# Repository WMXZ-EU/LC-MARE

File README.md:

# LC-MARE
Low-Cost Marine Acoustic REcorder. See detailed info in different folders
 
Actual preferred firmware verson is adalogger_V3

## Content
### 3D-models
contains some stl files for 3D printing
### adalogger_V2
first LC-Mare firmware uses only adalogger RP2040. Suitable for single hydrophone and sampling frequency up to 96 kHz
### adalogger_V3
improved LC-Mare firmware 
- for adalogger RP2040 (single hydrophone up to 96 kHz sampling frequency)
- for rp2350 based adafruit feather (stereo and up to 384 kHz sampling frequency)
### microPAM_V3
improved version of adalogger_V3 for three MCU types (RP2040, RP2350, Teensy4.1)
all for sampling frequency up to 384 kHz

As of Nov-2026, this is the suggested firmware.

Read the README.pdf and setup.pdf for general description and setup instructions

the latest release may be found in

https://github.com/WMXZ-EU/LC-MARE/releases/latest/download/microPAM_V3.zip

### Documents
different files describing project and hardware construction
### KICAD
hardware desigh files for
- ADC (ADC_V2)
- preamp (PreampV5-mare)
- Base board (LC_PAMV4b)
- Libraries (for KICAD)
### Python
contains python based setup and analysis scripts for adalogger software

Of importance is a GUI (LC_Mare.py) that provides access to basic operations, like inspecting LC_mare file parameters, visualizing time series and spectra, to configure the firmware, to convert compressed to wav files, and to upload latest firmware

An compiled version for adalogger software (.exe) with supporting libraries may be found in

https://github.com/WMXZ-EU/LC-MARE/releases/download/LC_Mare_v1.0.0/LC_Mare.zip

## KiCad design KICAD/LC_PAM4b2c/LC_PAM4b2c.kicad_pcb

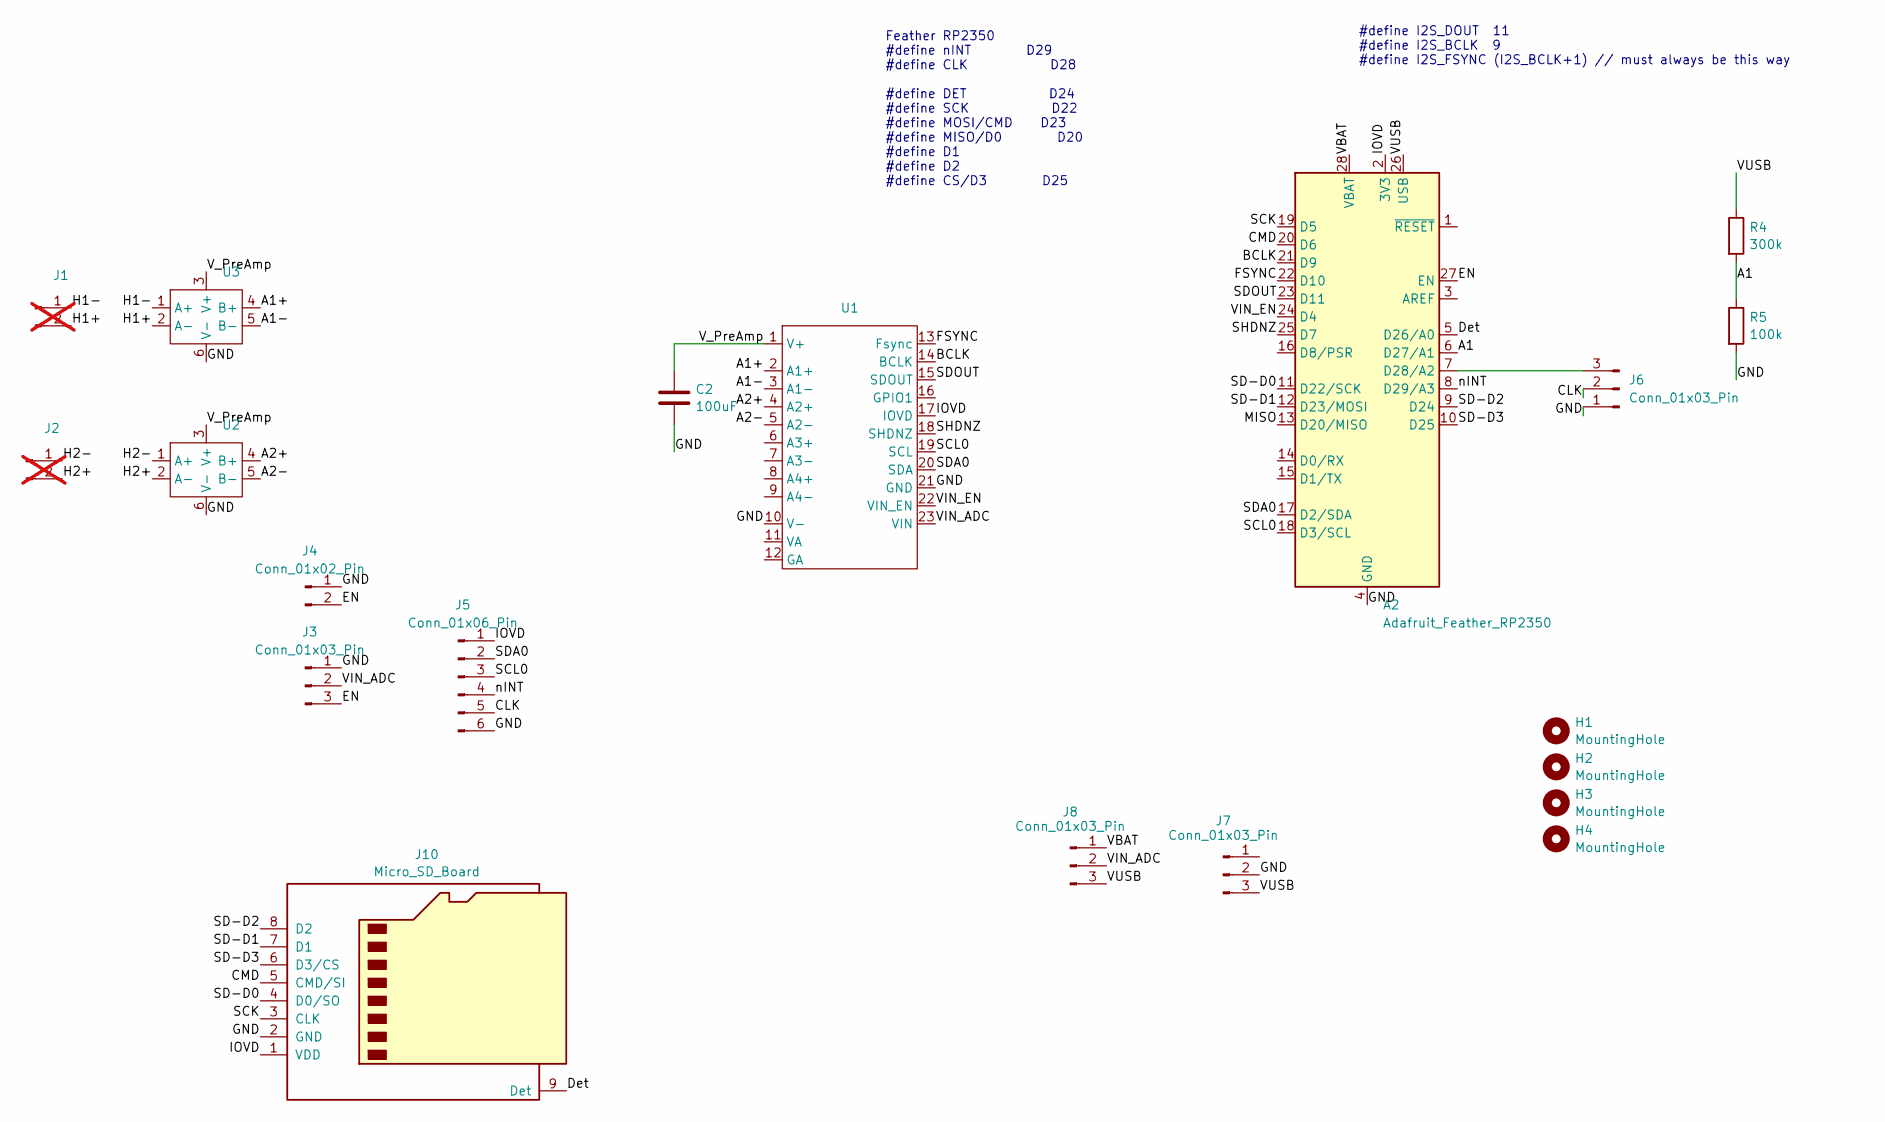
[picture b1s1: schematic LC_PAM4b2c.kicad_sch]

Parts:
A2: Adafruit_Feather_RP2350; Adafruit_Feather
C2: 100uF; CP_Radial_D4.0mm_P2.00mm
H1, H2, H3, H4: MountingHole; MountingHole_3.2mm_M3_DIN965
J1, J2: Conn_01x02_Male; Molex_PicoBlade_53048-0210_1x02_P1.25mm_Horizontal; not fitted
J3, J7, J8: Conn_01x03_Pin; PinHeader_1x03_P2.54mm_Vertical
J4: Conn_01x02_Pin; PinHeader_1x02_P2.54mm_Vertical
J5: Conn_01x06_Pin; PinHeader_1x06_P2.54mm_Vertical
J6: Conn_01x03_Pin; PinHeader_1x03_P1.27mm_Vertical
J10: Micro_SD_Board; uSD
R4: 300k; R_Axial_DIN0204_L3.6mm_D1.6mm_P1.90mm_Vertical
R5: 100k; R_Axial_DIN0204_L3.6mm_D1.6mm_P1.90mm_Vertical
U1: ADC_V2
U2, U3: preAmp2

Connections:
/A1: A2.6 (D27/A1), R4.2, R5.1
/A1+: U1.2 (A1+), U3.4 (B+)
/A1-: U1.3 (A1-), U3.5 (B-)
/A2+: U1.4 (A2+), U2.4 (B+)
/A2-: U1.5 (A2-), U2.5 (B-)
/BCLK: A2.21 (D9), U1.14 (BCLK)
/CLK: J5.5, J6.2
/CMD: A2.20 (D6), J10.5 (CMD/SI)
/Det: A2.5 (D26/A0), J10.9 (Det)
/EN: A2.27 (EN), J3.3, J4.2
/FSYNC: A2.22 (D10), U1.13 (Fsync)
/GND: A2.4 (GND), C2.2, J3.1, J4.1, J5.6, J6.1, J7.2, J10.2 (GND), R5.2, U1.10 (V-), U1.21 (GND), U2.6 (V-), U3.6 (V-)
/H1+: J1.2, U3.2 (A-)
/H1-: J1.1, U3.1 (A+)
/H2+: J2.2, U2.2 (A-)
/H2-: J2.1, U2.1 (A+)
/IOVD: A2.2 (3V3), J5.1, J10.1 (VDD), U1.17 (IOVD)
/MISO: A2.13 (D20/MISO)
/SCK: A2.19 (D5), J10.3 (CLK)
/SCL0: A2.18 (D3/SCL), J5.3, U1.19 (SCL)
/SD-D0: A2.11 (D22/SCK), J10.4 (D0/SO)
/SD-D1: A2.12 (D23/MOSI), J10.7 (D1)
/SD-D2: A2.9 (D24), J10.8 (D2)
/SD-D3: A2.10 (D25), J10.6 (D3/CS)
/SDA0: A2.17 (D2/SDA), J5.2, U1.20 (SDA)
/SDOUT: A2.23 (D11), U1.15 (SDOUT)
/SHDNZ: A2.25 (D7), U1.18 (SHDNZ)
/VBAT: A2.28 (VBAT), J8.1
/VIN_ADC: J3.2, J8.2, U1.23 (VIN)
/VIN_EN: A2.24 (D4), U1.22 (VIN_EN)
/VUSB: A2.26 (USB), J7.3, J8.3, R4.1
/V_PreAmp: C2.1, U1.1 (V+), U2.3 (V+), U3.3 (V+)
/nINT: A2.8 (D29/A3), J5.4
unnamed: A2.7 (D28/A2), J6.3

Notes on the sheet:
Feather RP2350 #define nINT D29 #define CLK D28 #define DET D24 #define SCK D22 #define MOSI/CMD D23 #define MISO/D0 D20 #define D1 #define D2 #define CS/D3 D25
#define I2S_DOUT 11 #define I2S_BCLK 9 #define I2S_FSYNC (I2S_BCLK+1) // must always be this way

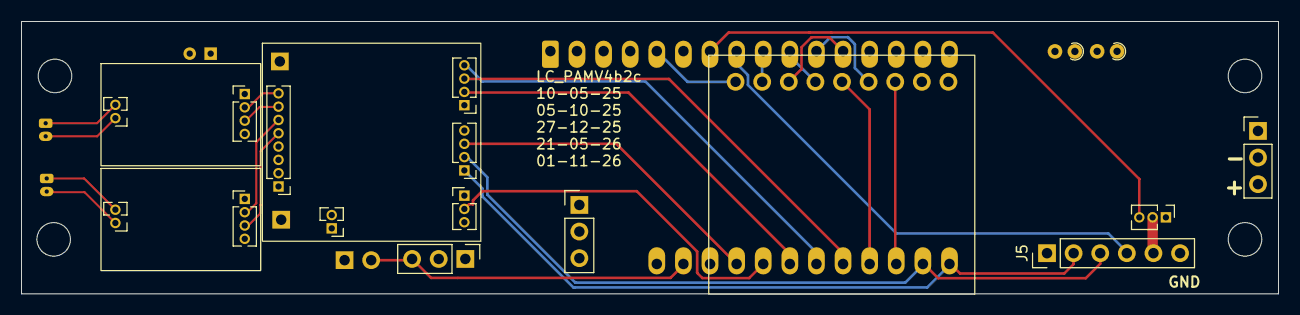
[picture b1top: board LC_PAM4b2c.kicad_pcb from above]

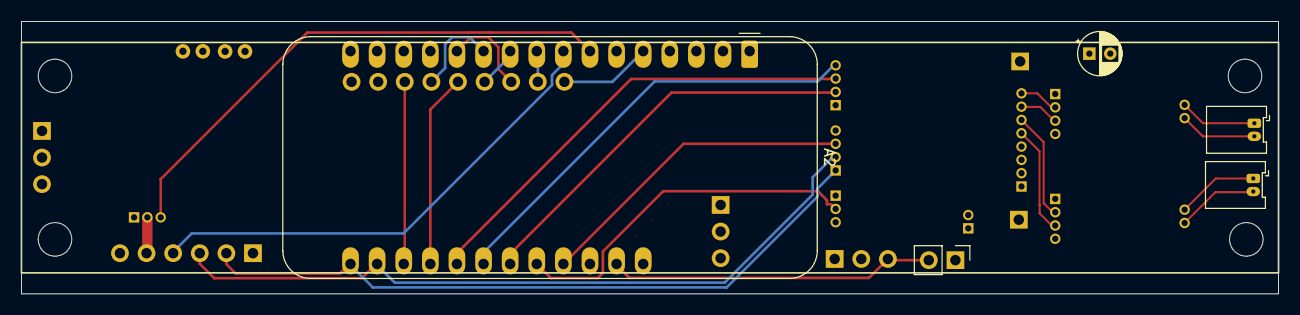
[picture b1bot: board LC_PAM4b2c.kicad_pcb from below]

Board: 4 copper layers, 120.0 x 26.0 mm, 20 parts (5 on the bottom side), 33 nets.

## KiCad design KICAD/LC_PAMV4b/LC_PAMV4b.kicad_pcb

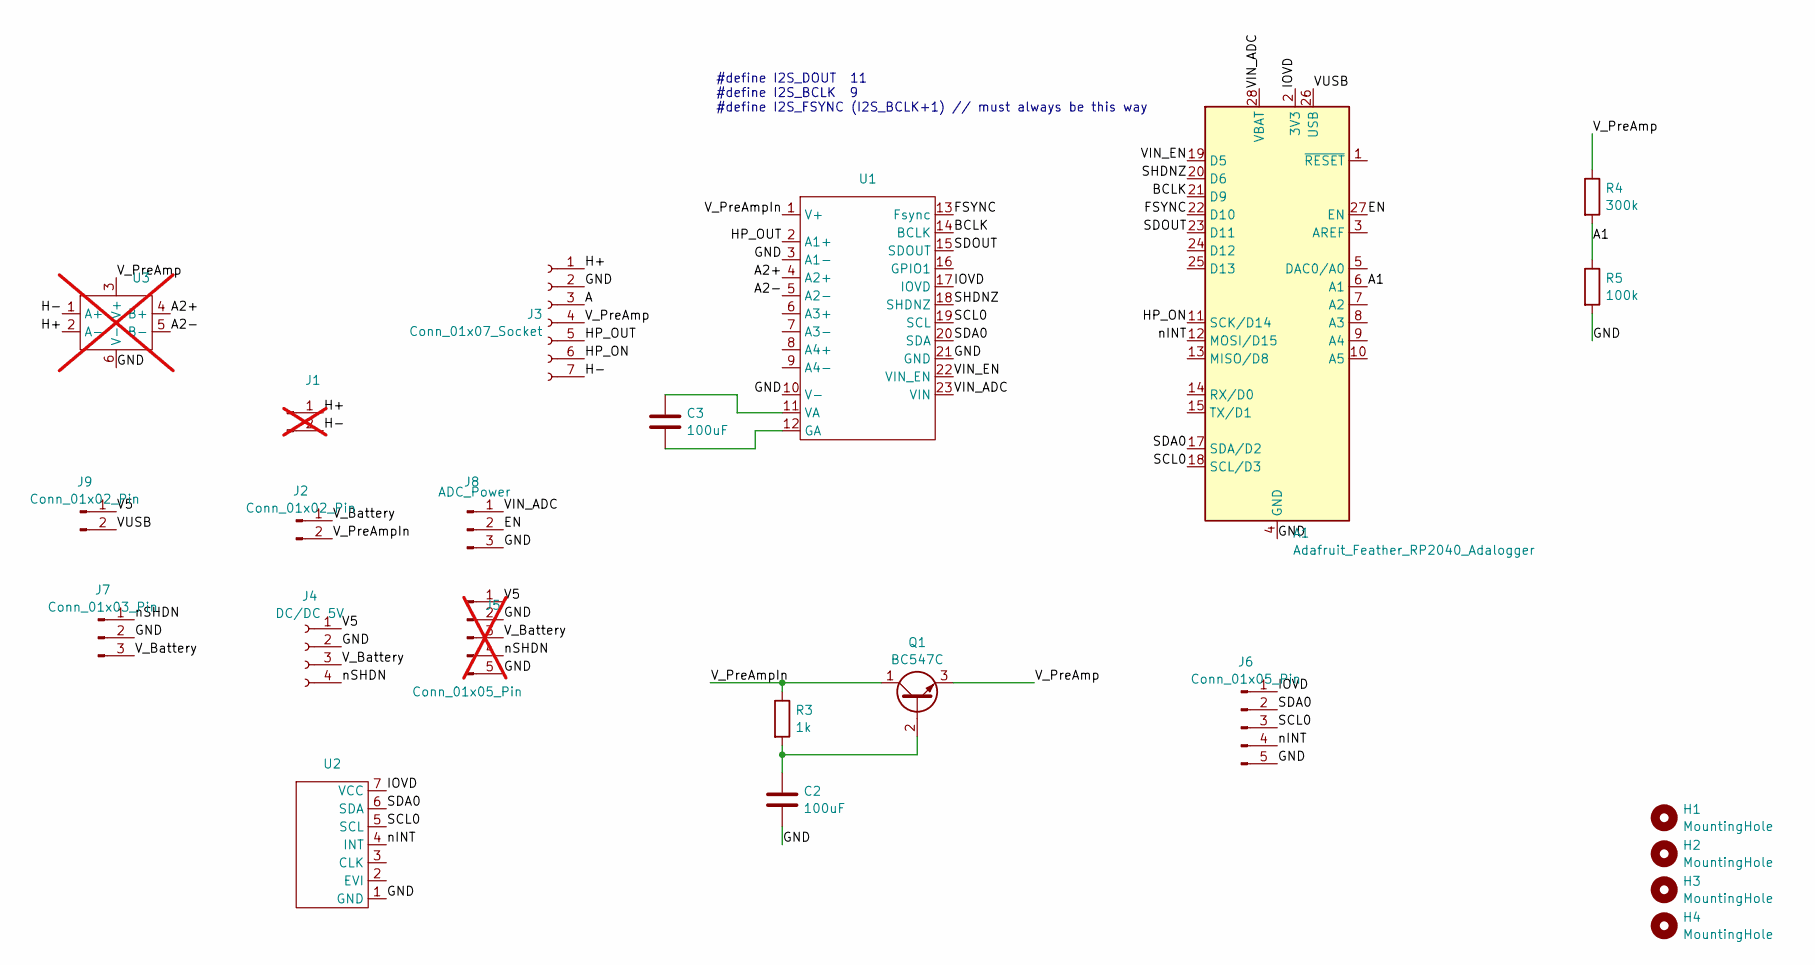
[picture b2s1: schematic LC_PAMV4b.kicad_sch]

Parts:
A1: Adafruit_Feather_RP2040_Adalogger; Adafruit_Feather_WithMountingHoles
C2, C3: 100uF; CP_Radial_D4.0mm_P2.00mm
H1, H2, H3, H4: MountingHole; MountingHole_3.2mm_M3_DIN965
J1: Conn_01x02_Male; Molex_PicoBlade_53048-0210_1x02_P1.25mm_Horizontal; not fitted
J2, J9: Conn_01x02_Pin; PinHeader_1x02_P2.00mm_Vertical
J3: Conn_01x07_Socket; HPAB
J4: DC/DC 5V; PinHeader_1x04_P2.54mm_Vertical
J5: Conn_01x05_Pin; PinHeader_1x05_P2.54mm_Vertical; not fitted
J6: Conn_01x05_Pin; PinHeader_1x05_P2.54mm_Vertical
J7: Conn_01x03_Pin; PinHeader_1x03_P2.54mm_Vertical
J8: ADC_Power; PinHeader_1x03_P2.54mm_Vertical
Q1: BC547C; TO-92_Inline
R3: 1k; R_Axial_DIN0204_L3.6mm_D1.6mm_P1.90mm_Vertical
R4: 300k; R_Axial_DIN0204_L3.6mm_D1.6mm_P1.90mm_Vertical
R5: 100k; R_Axial_DIN0204_L3.6mm_D1.6mm_P1.90mm_Vertical
U1: ADC_V2
U2: rtc2
U3: preAmp2; not fitted

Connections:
/A: J3.3
/A1: A1.6 (A1), R4.2, R5.1
/A2+: U1.4 (A2+), U3.4 (B+)
/A2-: U1.5 (A2-), U3.5 (B-)
/BCLK: A1.21 (D9), U1.14 (BCLK)
/EN: A1.27 (EN), J8.2
/FSYNC: A1.22 (D10), U1.13 (Fsync)
/GND: A1.4 (GND), A1.16 (GND), C2.2, J3.2, J4.2, J5.2, J5.5, J6.5, J7.2, J8.3, R5.2, U1.3 (A1-), U1.10 (V-), U1.21 (GND), U2.1 (GND), U3.6 (V-)
/H+: J1.1, J3.1, U3.2 (A-)
/H-: J1.2, J3.7, U3.1 (A+)
/HP_ON: A1.11 (SCK/D14), J3.6
/HP_OUT: J3.5, U1.2 (A1+)
/IOVD: A1.2 (3V3), J6.1, U1.17 (IOVD), U2.7 (VCC)
/SCL0: A1.18 (SCL/D3), J6.3, U1.19 (SCL), U2.5 (SCL)
/SDA0: A1.17 (SDA/D2), J6.2, U1.20 (SDA), U2.6 (SDA)
/SDOUT: A1.23 (D11), U1.15 (SDOUT)
/SHDNZ: A1.20 (D6), U1.18 (SHDNZ)
/V5: J4.1, J5.1, J9.1
/VIN_ADC: A1.28 (VBAT), J8.1, U1.23 (VIN)
/VIN_EN: A1.19 (D5), U1.22 (VIN_EN)
/VUSB: A1.26 (USB), J9.2
/V_Battery: J2.1, J4.3, J5.3, J7.3
/V_PreAmp: J3.4, Q1.3 (E), R4.1, U3.3 (V+)
/V_PreAmpIn: J2.2, Q1.1 (C), R3.1, U1.1 (V+)
/nINT: A1.12 (MOSI/D15), J6.4, U2.4 (INT)
/nSHDN: J4.4, J5.4, J7.1
unnamed: C2.1, Q1.2 (B), R3.2
unnamed: C3.2, U1.12 (GA)
unnamed: C3.1, U1.11 (VA)

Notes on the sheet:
#define I2S_DOUT 11 #define I2S_BCLK 9 #define I2S_FSYNC (I2S_BCLK+1) // must always be this way

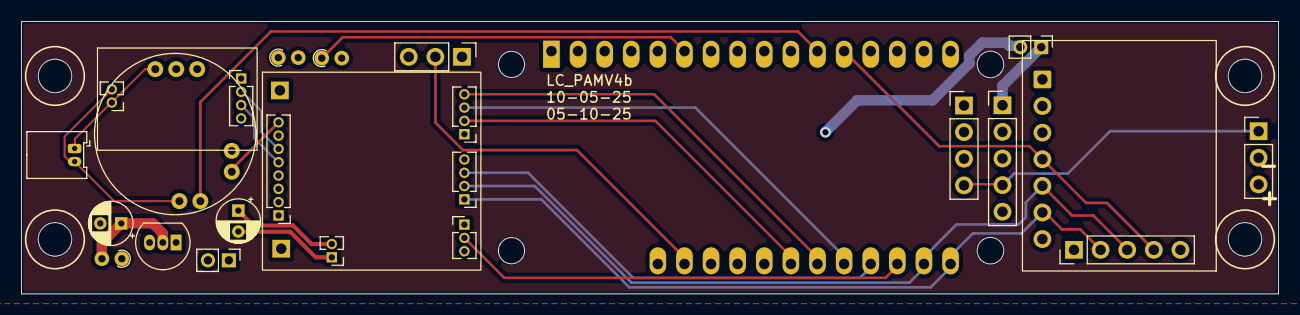
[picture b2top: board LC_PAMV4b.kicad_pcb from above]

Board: 4 copper layers, 120.0 x 26.0 mm, 24 parts (1 on the bottom side), 28 nets.

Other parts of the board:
J10: rtc; rtc2

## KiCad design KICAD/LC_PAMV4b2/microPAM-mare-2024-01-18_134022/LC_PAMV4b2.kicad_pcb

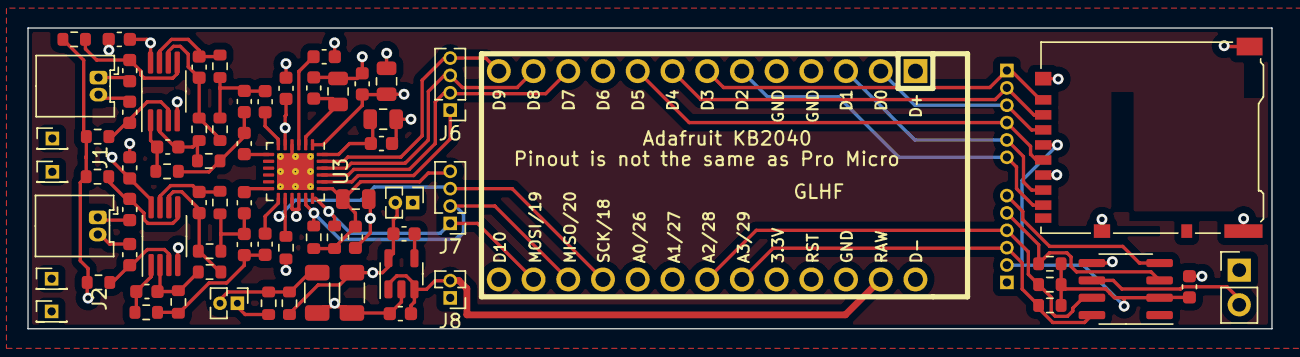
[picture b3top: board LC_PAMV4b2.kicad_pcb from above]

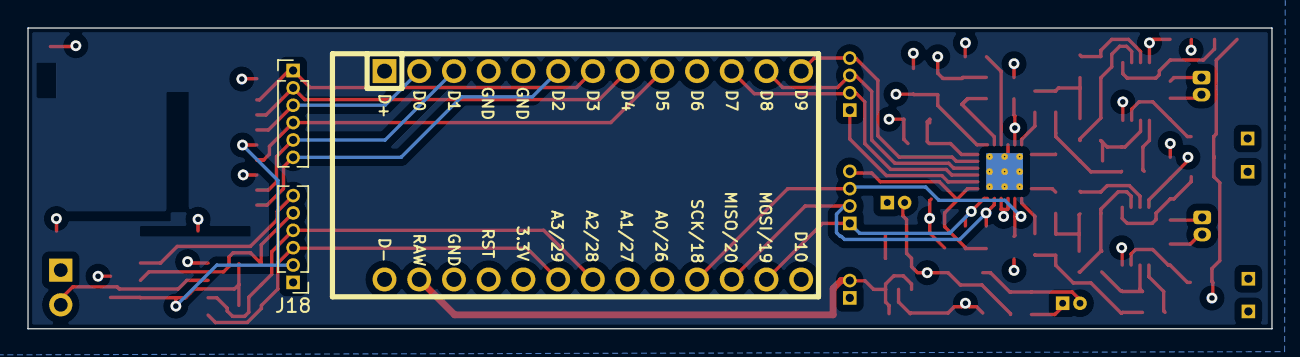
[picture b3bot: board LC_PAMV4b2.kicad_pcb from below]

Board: 4 copper layers, 91.0 x 22.0 mm, 74 parts (2 on the bottom side), 52 nets.

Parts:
C1, C2, C7, C8, C11, C12, C18, C19, C24, C28: 1u; C_0603_1608Metric
C3, C4, C9, C10: 15p; C_0603_1608Metric
C5, C6, C15, C16, C20, C23, C27, C29, C101: 0.1u; C_0603_1608Metric
C13, C14, C30: 10u; C_0805_2012Metric
C17, C22: 2700p; C_0603_1608Metric
C21: 1u; C_0805_2012Metric
C25, C26: 47u; C_1206_3216Metric
J1, J2: Conn_01x02_Male; Molex_PicoBlade_53048-0210_1x02_P1.25mm_Horizontal
J3, J4, J5, J11: Conn_01x01_Pin; PinHeader_1x01_P1.27mm_Vertical
J6, J7: Conn_01x04; PinHeader_1x04_P1.27mm_Vertical
J8: Conn_01x02; PinHeader_1x02_P1.27mm_Vertical
J9, J10: Conn_01x02_Pin; PinHeader_1x02_P1.27mm_Vertical
J14, J18: Conn_01x06_Pin; PinHeader_1x06_P1.27mm_Vertical
J15: Conn_01x02_Pin; PinHeader_1x02_P2.54mm_Vertical
J16: Micro_SD_Card_Det_Hirose_DM3AT; microSD_HC_Hirose_DM3AT-SF-PEJM5
R1, R7, R8, R14, R16: 10k; R_0603_1608Metric
R2, R3, R9, R10: 2M; R_0603_1608Metric
R4, R11: 1k; R_0603_1608Metric
R5, R6, R12, R13: 49R; R_0603_1608Metric
R15, R18, R101, R102, R103: 4.7k; R_0603_1608Metric
R17, R19: 100k; R_0603_1608Metric
U1, U2: AD8656; MSOP-8_3x3mm_P0.65mm
U3: TLV320ADC6140; QFN-24-1EP_4x4mm_P0.5mm_EP2.7x2.7mm_ThermalVias
U4: MIC5219-3.3YM5; SOT-23-5
U51: kb2040
U102: DS3232M; SOIC-8_3.9x4.9mm_P1.27mm

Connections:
/AVDD: C5.1, C6.1, C20.1, C21.1, C23.2, C25.1, J9.2, R17.1, U1.8 (V+), U2.8 (V+), U3.1 (AVDD), U4.5 (OUT)
/BCLK: J6.3, U3.22 (BCLK), U51.12 (D8)
/CMD: J14.3, J16.3 (CMD), U51.2 (D0)
/DAT0: J14.5, J16.7 (DAT0), U51.3 (D1)
/DAT1: J14.6, J16.8 (DAT1), U51.6 (D2)
/DAT2: J14.1, J16.1 (DAT2), U51.7 (D3)
/DAT3: J14.2, J16.2 (DAT3/CD), U51.8 (D4)
/DIn: J6.2, U3.21 (SDOUT), U51.11 (D7)
/FSYNC: J6.4, U3.23 (FSYNC), U51.13 (D9)
/GPIO1: J6.1, U3.20 (GPIO1)
/MicBias: C11.1, J3.1, J4.1, U3.5 (MICBIAS)
/SCK: J14.4, J16.5 (CLK), U51.9 (D5)
/SCL1: J7.2, R15.2, U3.17 (SCL_MOSI), U51.24 (MISO/20)
/SDA1: J7.1, R18.2, U3.18 (SDA_SSZ), U51.25 (MOSI/19)
/SHDNZ: J7.3, R16.2, U3.14 (SHDNZ), U51.23 (SCK/18)
/VCOM: C26.1, J10.2, R2.2, R3.1, R9.2, R10.1, R17.2, R19.1
/VIN: C27.2, J8.2, U4.1 (IN), U4.3 (EN), U51.15 (RAW)
/nRST: J18.6, U102.4 (~RST)
GND: C5.2, C6.2, C11.2, C12.2, C13.2, C14.2, C15.2, C16.2, C20.2, C21.2, C25.2, C26.2, C27.1, C29.2, C30.2, C101.2, J5.1, J8.1, J9.1, J10.1, J11.1, J15.1, J16.6 (VSS), J16.11 (SHIELD), J18.1, R16.1, R19.2, U1.4 (V-), U2.4 (V-), U3.4 (AVSS), U3.15 (ADDR1_MISO), U3.16 (ADDR0_SCLK), U3.25 (PAD), U4.2 (GND), U51.4 (GND), U51.5 (GND), U51.16 (GND), U102.5 (GND)
IOVD: C29.1, C30.1, C101.1, J7.4, J16.4 (VDD), J18.2, R15.1, R18.1, R101.1, R102.1, R103.1, U3.19 (IOVD), U51.18 (3.3v), U102.2 (VCC)
unnamed: C3.2, R5.2, U1.1
unnamed: C4.1, R6.2, U1.7
unnamed: C9.2, R12.2, U2.1
unnamed: C10.1, R13.2, U2.7
unnamed: C17.1, C19.2, R1.1, R5.1
unnamed: C17.2, C18.2, R6.1, R7.1
unnamed: C22.1, C28.2, R8.1, R12.1
unnamed: C22.2, C24.2, R13.1, R14.1
unnamed: C2.2, J1.1
unnamed: C1.2, J1.2
unnamed: C8.2, J2.1
unnamed: C7.2, J2.2
unnamed: C1.1, R2.1, U1.3 (+)
unnamed: C3.1, R1.2, R4.1, U1.2 (-)
unnamed: C2.1, R3.2, U1.5 (+)
unnamed: C4.2, R4.2, R7.2, U1.6 (-)
unnamed: C7.1, R9.1, U2.3 (+)
unnamed: C9.1, R8.2, R11.1, U2.2 (-)
unnamed: C8.1, R10.2, U2.5 (+)
unnamed: C10.2, R11.2, R14.2, U2.6 (-)
unnamed: C13.1, C16.1, U3.2 (AREG)
unnamed: C14.1, C15.1, U3.24 (DREG)
unnamed: C19.1, U3.7 (IN1M_GPO1)
unnamed: C18.1, U3.6 (IN1P_GPI1)
unnamed: C28.1, U3.13 (IN4M_GPO4)
unnamed: C24.1, U3.12 (IN4P_GPI4)
unnamed: C12.1, U3.3 (VREF)
unnamed: C23.1, U4.4 (BP)
SCL0: J18.3, R101.2, U51.19 (A3/29), U102.8 (SCL)
SDA0: J18.4, R102.2, U51.20 (A2/28), U102.7 (SDA)
VBAT: J15.2, U102.6 (VBAT)
nINT: J18.5, R103.2, U102.3 (~INT/SQW)

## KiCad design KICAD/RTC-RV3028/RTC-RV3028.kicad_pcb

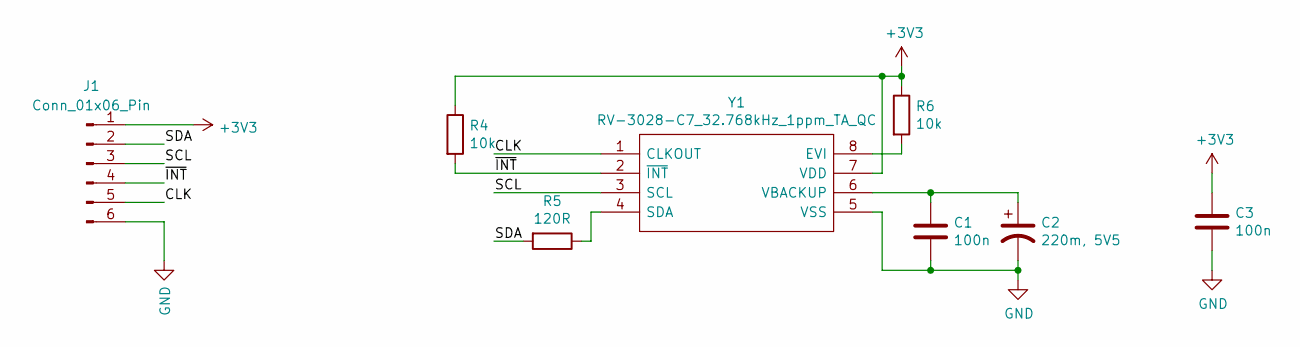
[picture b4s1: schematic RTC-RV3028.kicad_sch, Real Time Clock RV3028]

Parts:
C1, C3: 100n; C_0603_1608Metric
C2: 220m, 5V5; Kemet_FC_10.5X5.5
J1: Conn_01x06_Pin; PinHeader_1x06_P2.54mm_Vertical
R4, R6: 10k; R_0603_1608Metric
R5: 120R; C_0603_1608Metric
Y1: RV-3028-C7_32.768kHz_1ppm_TA_QC; MicroCrystal_RV3028C7; Mouser Part Number 428-203591-MG01

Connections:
+3V3: C3.1, J1.1, R4.1, R6.1, Y1.7 (VDD)
/CLK: J1.5, Y1.1 (CLKOUT)
/SCL: J1.3, Y1.3 (SCL)
/SDA: J1.2, R5.2
/~INT: J1.4, R4.2, Y1.2 (~INT)
GND: C1.2, C2.2, C3.2, J1.6, Y1.5 (VSS)
unnamed: R6.2, Y1.8 (EVI)
unnamed: R5.1, Y1.4 (SDA)
unnamed: C1.1, C2.1, Y1.6 (VBACKUP)

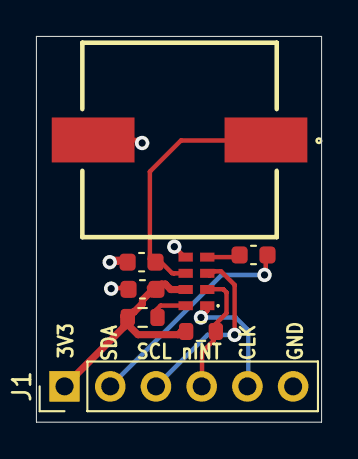
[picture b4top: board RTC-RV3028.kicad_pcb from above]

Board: 2 copper layers, 15.8 x 21.4 mm, 8 parts (0 on the bottom side), 9 nets.

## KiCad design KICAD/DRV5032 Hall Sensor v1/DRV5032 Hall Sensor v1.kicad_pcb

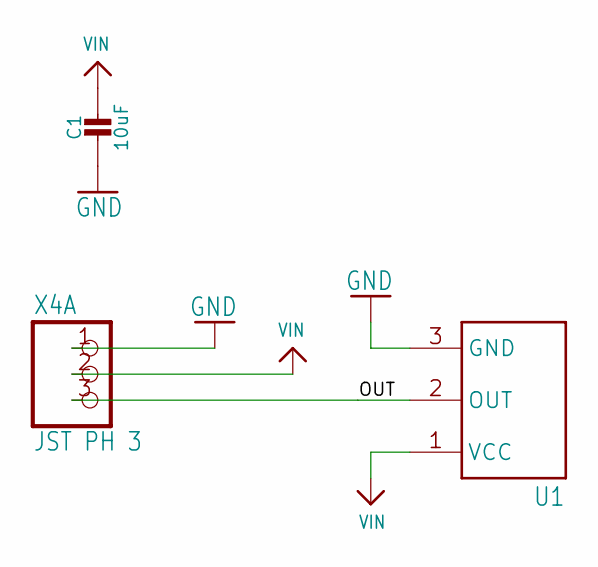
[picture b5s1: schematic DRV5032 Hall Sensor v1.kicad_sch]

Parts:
C1: 10uF; 0805-NO
U1: DRV5055A1QDBZT; SOT95P237X112-3N
X4: JST PH 3; JSTPH3

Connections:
GND: C1.2, U1.3 (GND), X4.1
OUT: U1.2 (OUT), X4.3
VIN: C1.1, U1.1 (VCC), X4.2

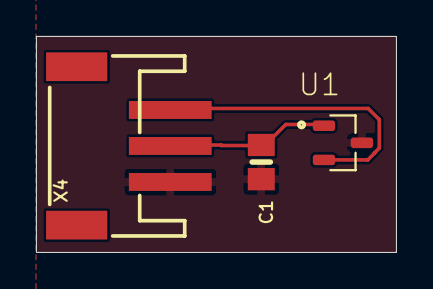
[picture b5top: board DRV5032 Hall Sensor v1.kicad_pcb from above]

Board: 2 copper layers, 20.0 x 12.0 mm, 3 parts (0 on the bottom side), 3 nets.

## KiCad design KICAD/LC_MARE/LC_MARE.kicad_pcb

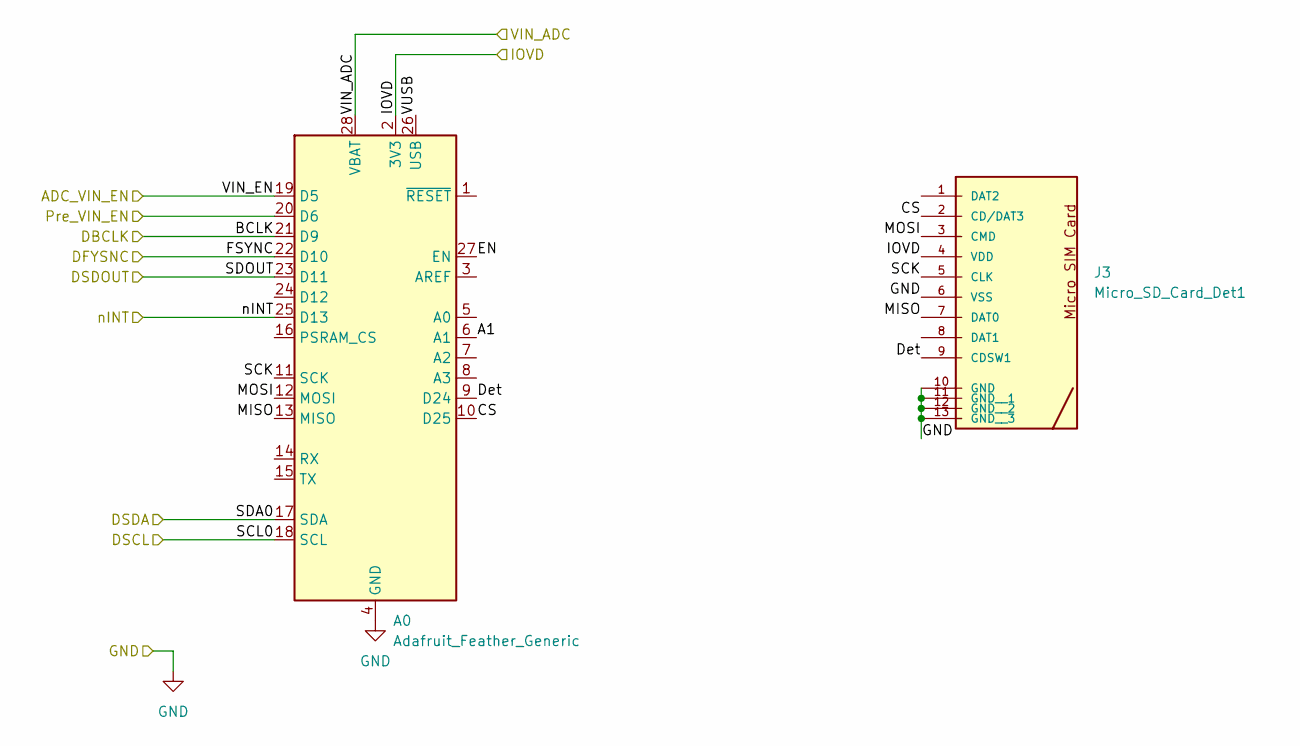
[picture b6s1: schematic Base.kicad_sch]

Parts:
A0: Adafruit_Feather_Generic; Adafruit_Feather
J3: Micro_SD_Card_Det1; 693071020811

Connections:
/ADC/BCLK: A0.21 (D9); also elsewhere on the board
/ADC/FSYNC: A0.22 (D10); also elsewhere on the board
/ADC/SDOUT: A0.23 (D11); also elsewhere on the board
/Base/A1: A0.6 (A1)
/Base/CS: A0.10 (D25), J3.2 (CD/DAT3)
/Base/Det: A0.9 (D24), J3.9 (CDSW1)
/Base/EN: A0.27 (EN)
/Base/MISO: A0.13 (MISO), J3.7 (DAT0)
/Base/MOSI: A0.12 (MOSI), J3.3 (CMD)
/Base/SCK: A0.11 (SCK), J3.5 (CLK)
/Base/VIN_ADC: A0.28 (VBAT); also elsewhere on the board
/Base/VIN_EN: A0.19 (D5)
/Base/VUSB: A0.26 (USB)
/PreAmps/VIN_EN: A0.20 (D6); also elsewhere on the board
GND: A0.4 (GND), J3.6 (VSS), J3.10 (GND), J3.11 (GND__1), J3.12 (GND__2), J3.13 (GND__3); also elsewhere on the board
INT: A0.25 (D13); also elsewhere on the board
SCL: A0.18 (SCL); also elsewhere on the board
SDA: A0.17 (SDA); also elsewhere on the board
VCC: A0.2 (3V3), J3.4 (VDD); also elsewhere on the board

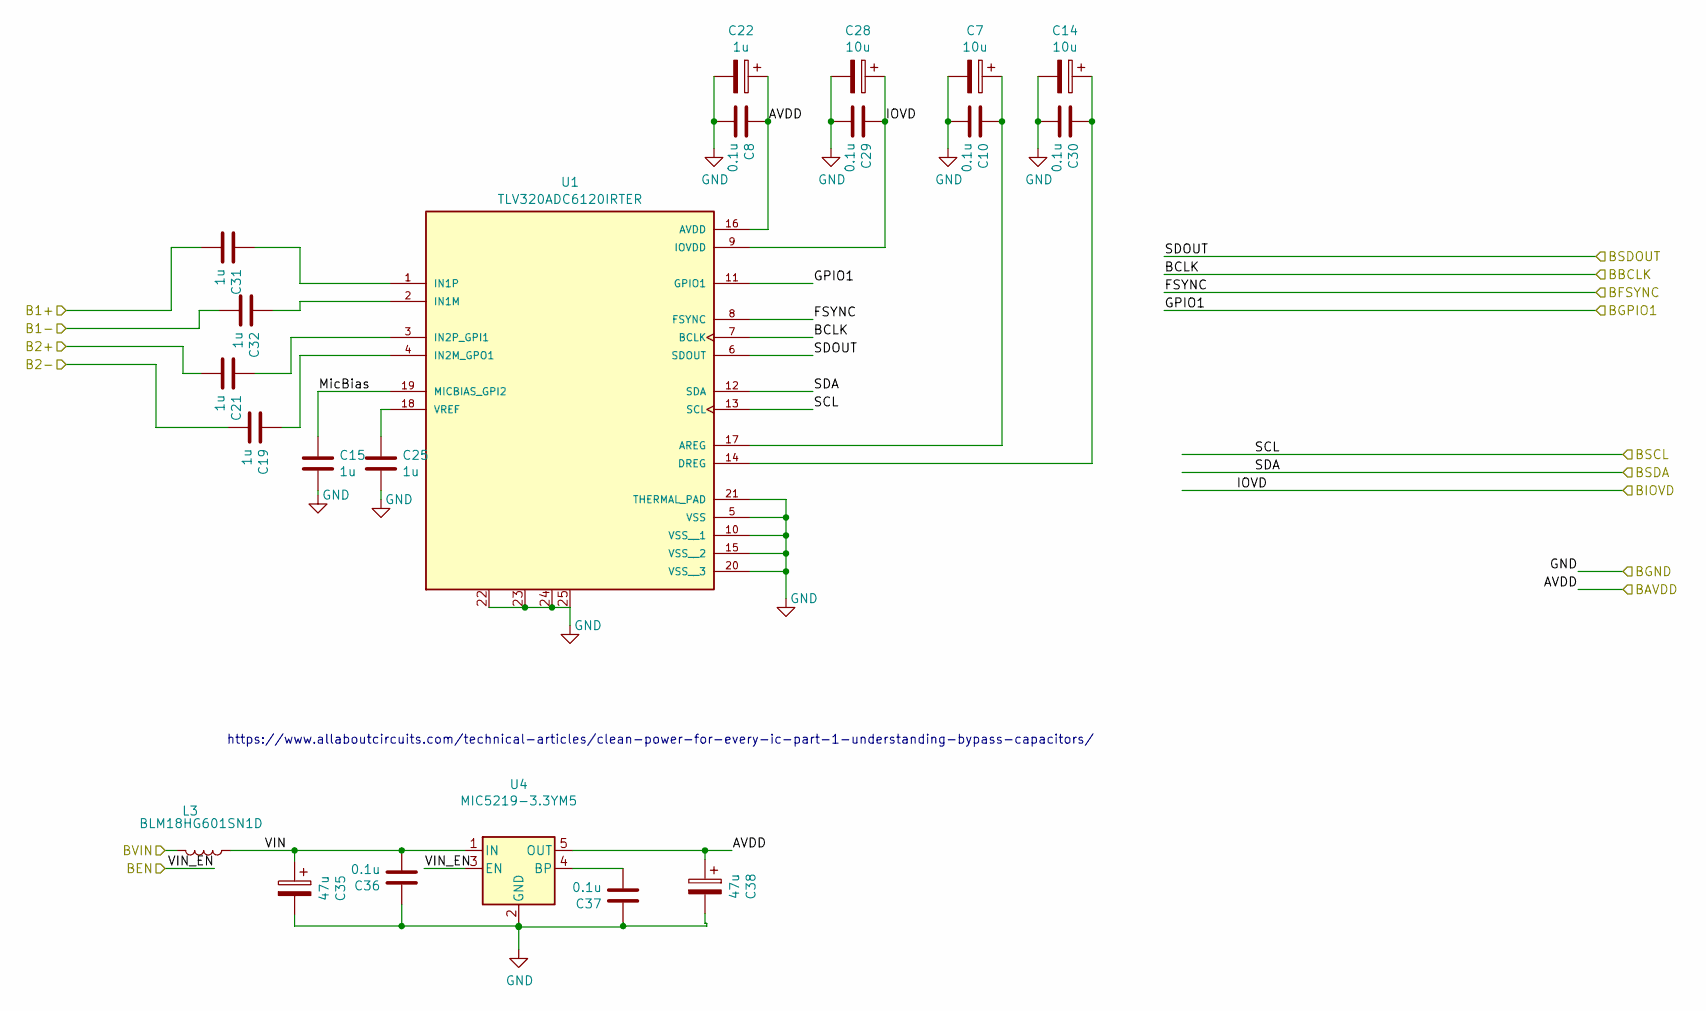
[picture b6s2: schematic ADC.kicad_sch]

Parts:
C7, C14, C28: 10u; CP_EIA-2012-15_AVX-P
C8, C10, C29, C30, C36, C37: 0.1u; C_0603_1608Metric
C15, C19, C21, C25, C31, C32: 1u; C_0603_1608Metric
C22: 1u; CP_EIA-2012-15_AVX-P
C35, C38: 47u; CP_EIA-3216-12_Kemet-S
L3: BLM18HG601SN1D; L_0603_1608Metric
U1: TLV320ADC6120IRTER; IC_TLV320ADC6120IRTER; PARTREV A
U4: MIC5219-3.3YM5; SOT-23-5

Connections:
/ADC/AVDD: C8.1, C22.1, C38.1, U1.16 (AVDD), U4.5 (OUT)
/ADC/B1+: C31.2; also elsewhere on the board
/ADC/B1-: C32.2; also elsewhere on the board
/ADC/BCLK: U1.7 (BCLK); also elsewhere on the board
/ADC/FSYNC: U1.8 (FSYNC); also elsewhere on the board
/ADC/GPIO1: U1.11 (GPIO1)
/ADC/MicBias: C15.1, U1.19 (MICBIAS_GPI2)
/ADC/SDOUT: U1.6 (SDOUT); also elsewhere on the board
/ADC/VIN: C35.1, C36.2, L3.1, U4.1 (IN)
/ADC/VIN_EN: U4.3 (EN)
/Base/VIN_ADC: L3.2; also elsewhere on the board
/PreAmps/A2+: C19.2; also elsewhere on the board
/PreAmps/A2-: C21.2; also elsewhere on the board
GND: C7.2, C8.2, C10.2, C14.2, C15.2, C22.2, C25.2, C28.2, C29.2, C30.2, C35.2, C36.1, C37.1, C38.2, U1.5 (VSS), U1.10 (VSS__1), U1.15 (VSS__2), U1.20 (VSS__3), U1.21 (THERMAL_PAD), U1.22, U1.23, U1.24, U1.25, U4.2 (GND); also elsewhere on the board
unnamed: C7.1, C10.1, U1.17 (AREG)
unnamed: C14.1, C30.1, U1.14 (DREG)
unnamed: C32.1, U1.2 (IN1M)
unnamed: C31.1, U1.1 (IN1P)
unnamed: C19.1, U1.4 (IN2M_GPO1)
unnamed: C21.1, U1.3 (IN2P_GPI1)
unnamed: C25.1, U1.18 (VREF)
unnamed: C37.2, U4.4 (BP)
SCL: U1.13 (SCL); also elsewhere on the board
SDA: U1.12 (SDA); also elsewhere on the board
VCC: C28.1, C29.1, U1.9 (IOVDD); also elsewhere on the board

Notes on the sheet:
https://www.allaboutcircuits.com/technical-articles/clean-power-for-every-ic-part-1-understanding-bypass-capacitors/

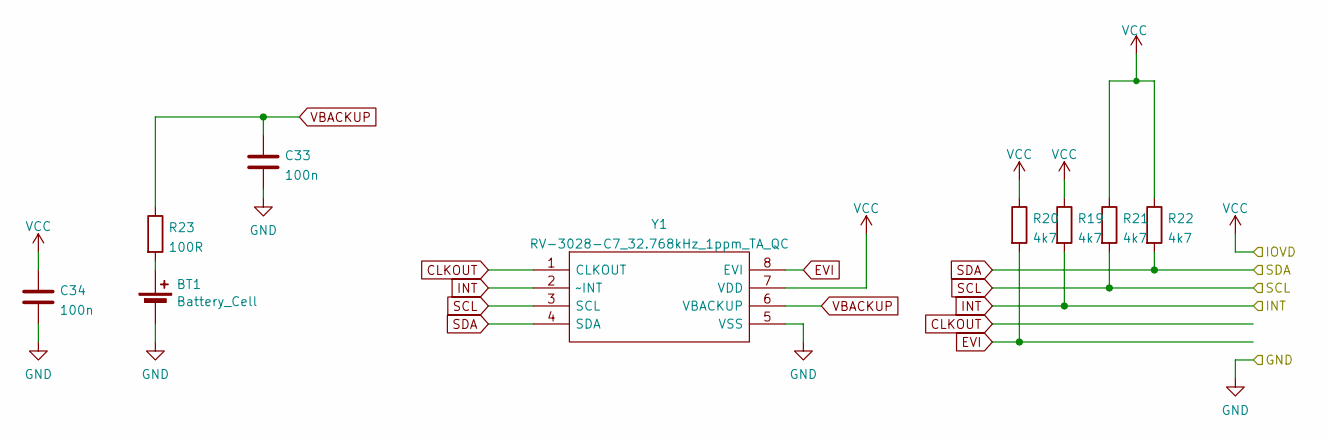
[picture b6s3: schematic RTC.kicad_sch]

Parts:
BT1: Battery_Cell; coin-cell
C33, C34: 100n; C_0603_1608Metric
R19, R20, R21, R22: 4k7; C_0603_1608Metric
R23: 100R; C_0603_1608Metric
Y1: RV-3028-C7_32.768kHz_1ppm_TA_QC; IC_RV-3028-C7_32.768KHZ_1PPM-TA-QC; Mouser Part Number 428-203591-MG01

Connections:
CLKOUT: Y1.1 (CLKOUT)
EVI: R20.2, Y1.8 (EVI)
GND: BT1.2 (-), C33.2, C34.2, Y1.5 (VSS); also elsewhere on the board
INT: R19.2, Y1.2 (~INT); also elsewhere on the board
unnamed: BT1.1 (+), R23.2
SCL: R21.2, Y1.3 (SCL); also elsewhere on the board
SDA: R22.2, Y1.4 (SDA); also elsewhere on the board
VBACKUP: C33.1, R23.1, Y1.6 (VBACKUP)
VCC: C34.1, R19.1, R20.1, R21.1, R22.1, Y1.7 (VDD); also elsewhere on the board

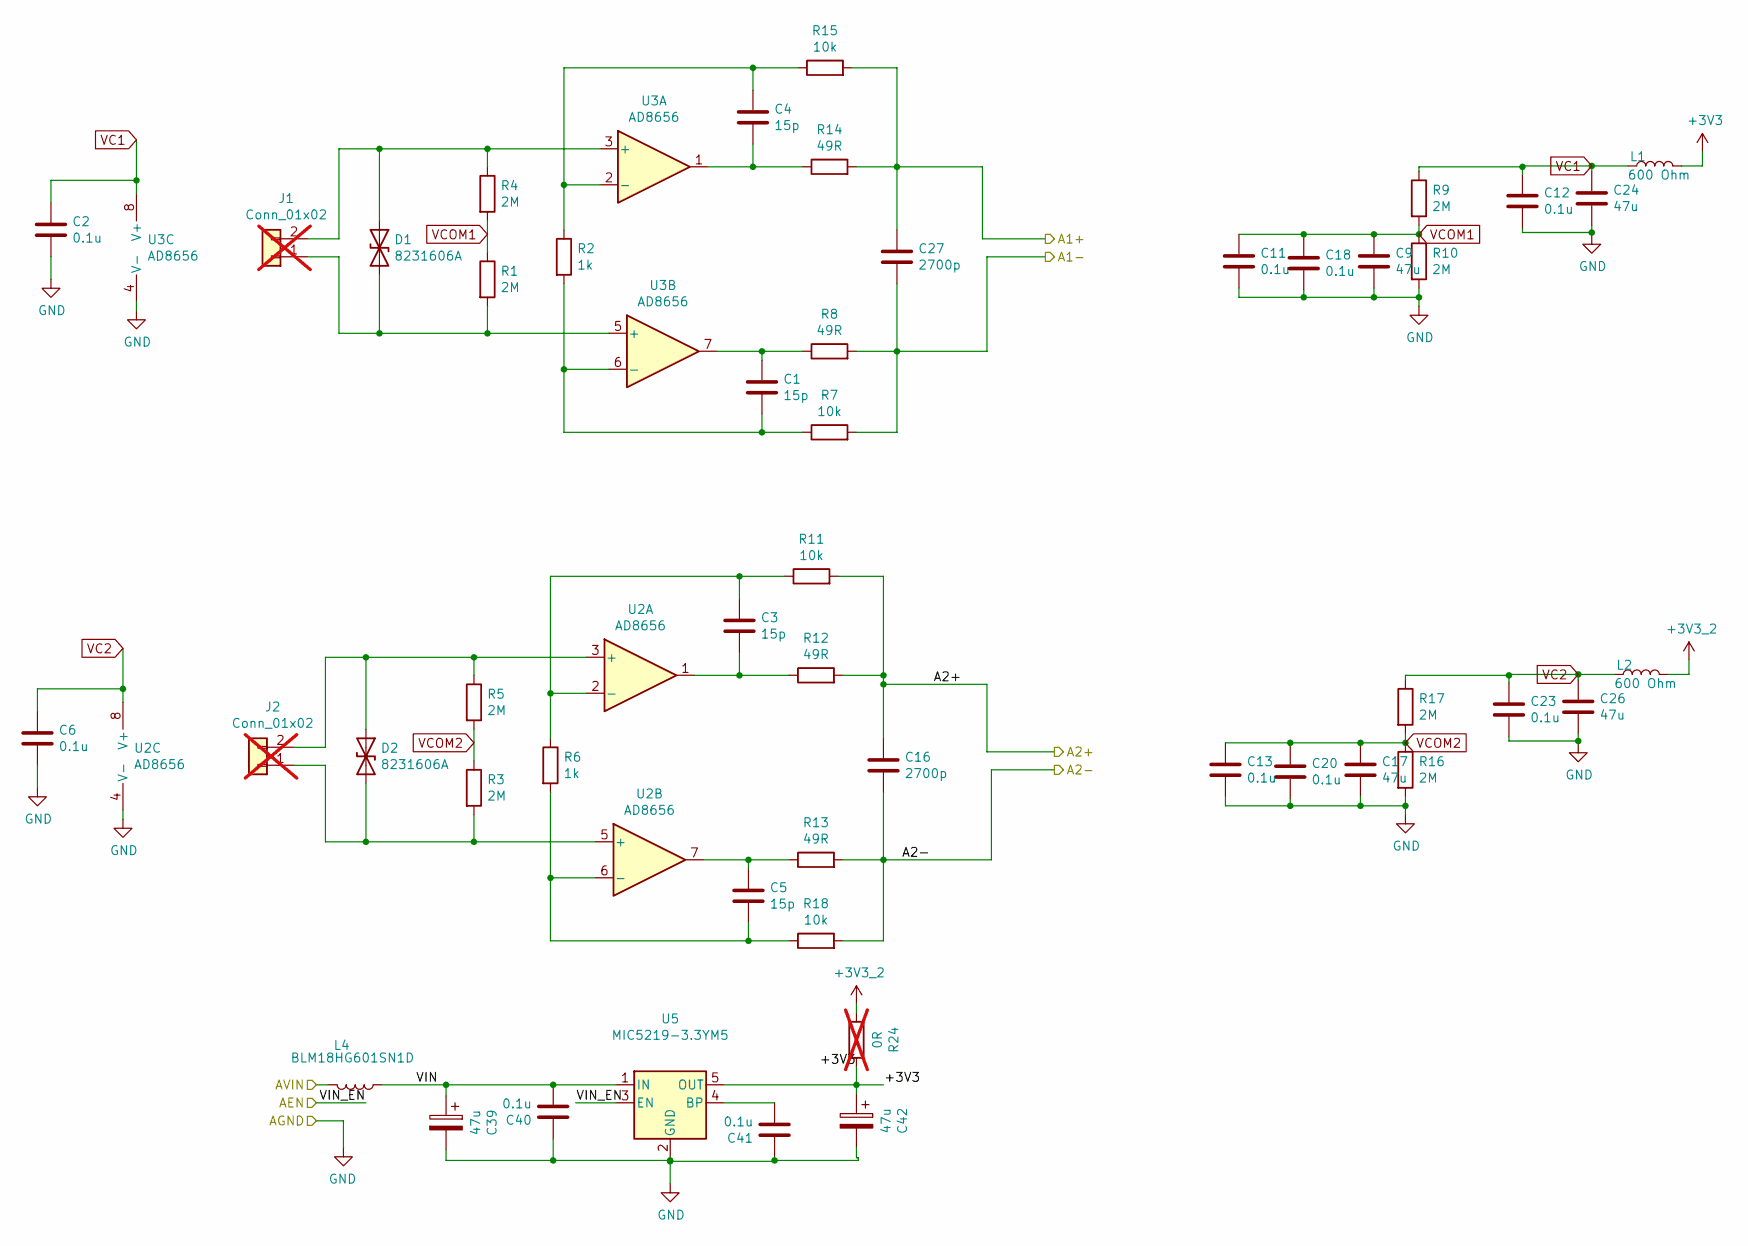
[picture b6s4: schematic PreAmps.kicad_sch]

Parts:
C1, C3, C4, C5: 15p; C_0402_1005Metric
C2, C6, C11, C12, C13, C18, C20, C23: 0.1u; C_0402_1005Metric
C9, C17, C24, C26: 47u; C_0805_2012Metric
C16, C27: 2700p; C_0402_1005Metric
C39, C42: 47u; CP_EIA-3216-12_Kemet-S
C40, C41: 0.1u; C_0603_1608Metric
D1, D2: 8231606A; D_0603_1608Metric
J1, J2: Conn_01x02; PinHeader_1x02_P1.27mm_Vertical; not fitted
L1, L2: 600 Ohm; L_0603_1608Metric
L4: BLM18HG601SN1D; L_0603_1608Metric
R1, R3, R4, R5, R9, R10, R16, R17: 2M; R_0402_1005Metric
R2, R6: 1k; R_0402_1005Metric
R7, R11, R15, R18: 10k; R_0402_1005Metric
R8, R12, R13, R14: 49R; R_0402_1005Metric
R24: 0R; R_0402_1005Metric; not fitted
U2, U3: AD8656; MSOP-8_3x3mm_P0.65mm
U5: MIC5219-3.3YM5; SOT-23-5

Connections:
+3V3: C42.1, L1.2, R24.2, U5.5 (OUT)
+3V3_2: L2.2, R24.1
/ADC/B1+: C27.2, R7.2, R8.2; also elsewhere on the board
/ADC/B1-: C27.1, R14.2, R15.2; also elsewhere on the board
/Base/VIN_ADC: L4.2; also elsewhere on the board
/PreAmps/A2+: C16.1, R11.2, R12.2; also elsewhere on the board
/PreAmps/A2-: C16.2, R13.2, R18.2; also elsewhere on the board
/PreAmps/VIN: C39.1, C40.2, L4.1, U5.1 (IN)
/PreAmps/VIN_EN: U5.3 (EN); also elsewhere on the board
GND: C2.2, C6.2, C9.2, C11.2, C12.2, C13.2, C17.2, C18.2, C20.2, C23.2, C24.2, C26.2, C39.2, C40.1, C41.1, C42.2, R10.2, R16.2, U2.4 (V-), U3.4 (V-), U5.2 (GND); also elsewhere on the board
unnamed: C1.1, R8.1, U3.7
unnamed: C3.2, R12.1, U2.1
unnamed: C4.2, R14.1, U3.1
unnamed: C5.1, R13.1, U2.7
unnamed: D1.1 (A1), J1.2, R4.1, U3.3 (+)
unnamed: D1.2 (A2), J1.1, R1.2, U3.5 (+)
unnamed: D2.1 (A1), J2.2, R5.1, U2.3 (+)
unnamed: D2.2 (A2), J2.1, R3.2, U2.5 (+)
unnamed: C3.1, R6.1, R11.1, U2.2 (-)
unnamed: C5.2, R6.2, R18.1, U2.6 (-)
unnamed: C4.1, R2.1, R15.1, U3.2 (-)
unnamed: C1.2, R2.2, R7.1, U3.6 (-)
unnamed: C41.2, U5.4 (BP)
VC1: C2.1, C12.1, C24.1, L1.1, R9.1, U3.8 (V+)
VC2: C6.1, C23.1, C26.1, L2.1, R17.1, U2.8 (V+)
VCOM1: C9.1, C11.1, C18.1, R1.1, R4.2, R9.2, R10.1
VCOM2: C13.1, C17.1, C20.1, R3.1, R5.2, R16.1, R17.2

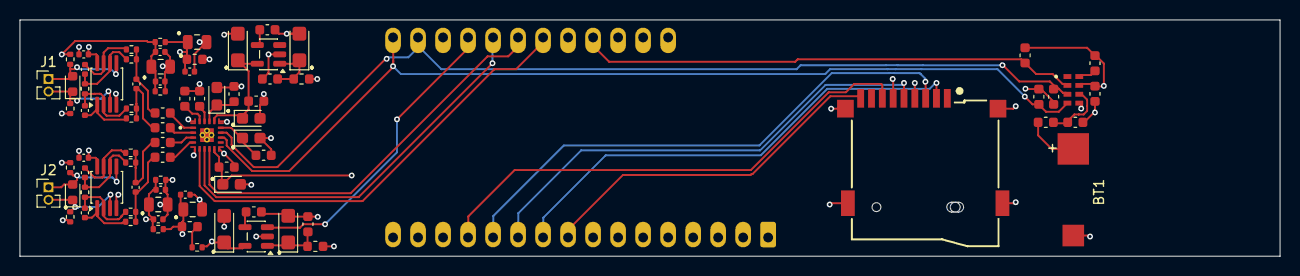
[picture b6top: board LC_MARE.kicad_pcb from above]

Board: 4 copper layers, 128.0 x 24.0 mm, 83 parts (1 on the bottom side), 53 nets.
